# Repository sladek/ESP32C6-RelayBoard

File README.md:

# ESP32C6-RelayBoard
Board with relays and sensors with ESP32C6 SOC.

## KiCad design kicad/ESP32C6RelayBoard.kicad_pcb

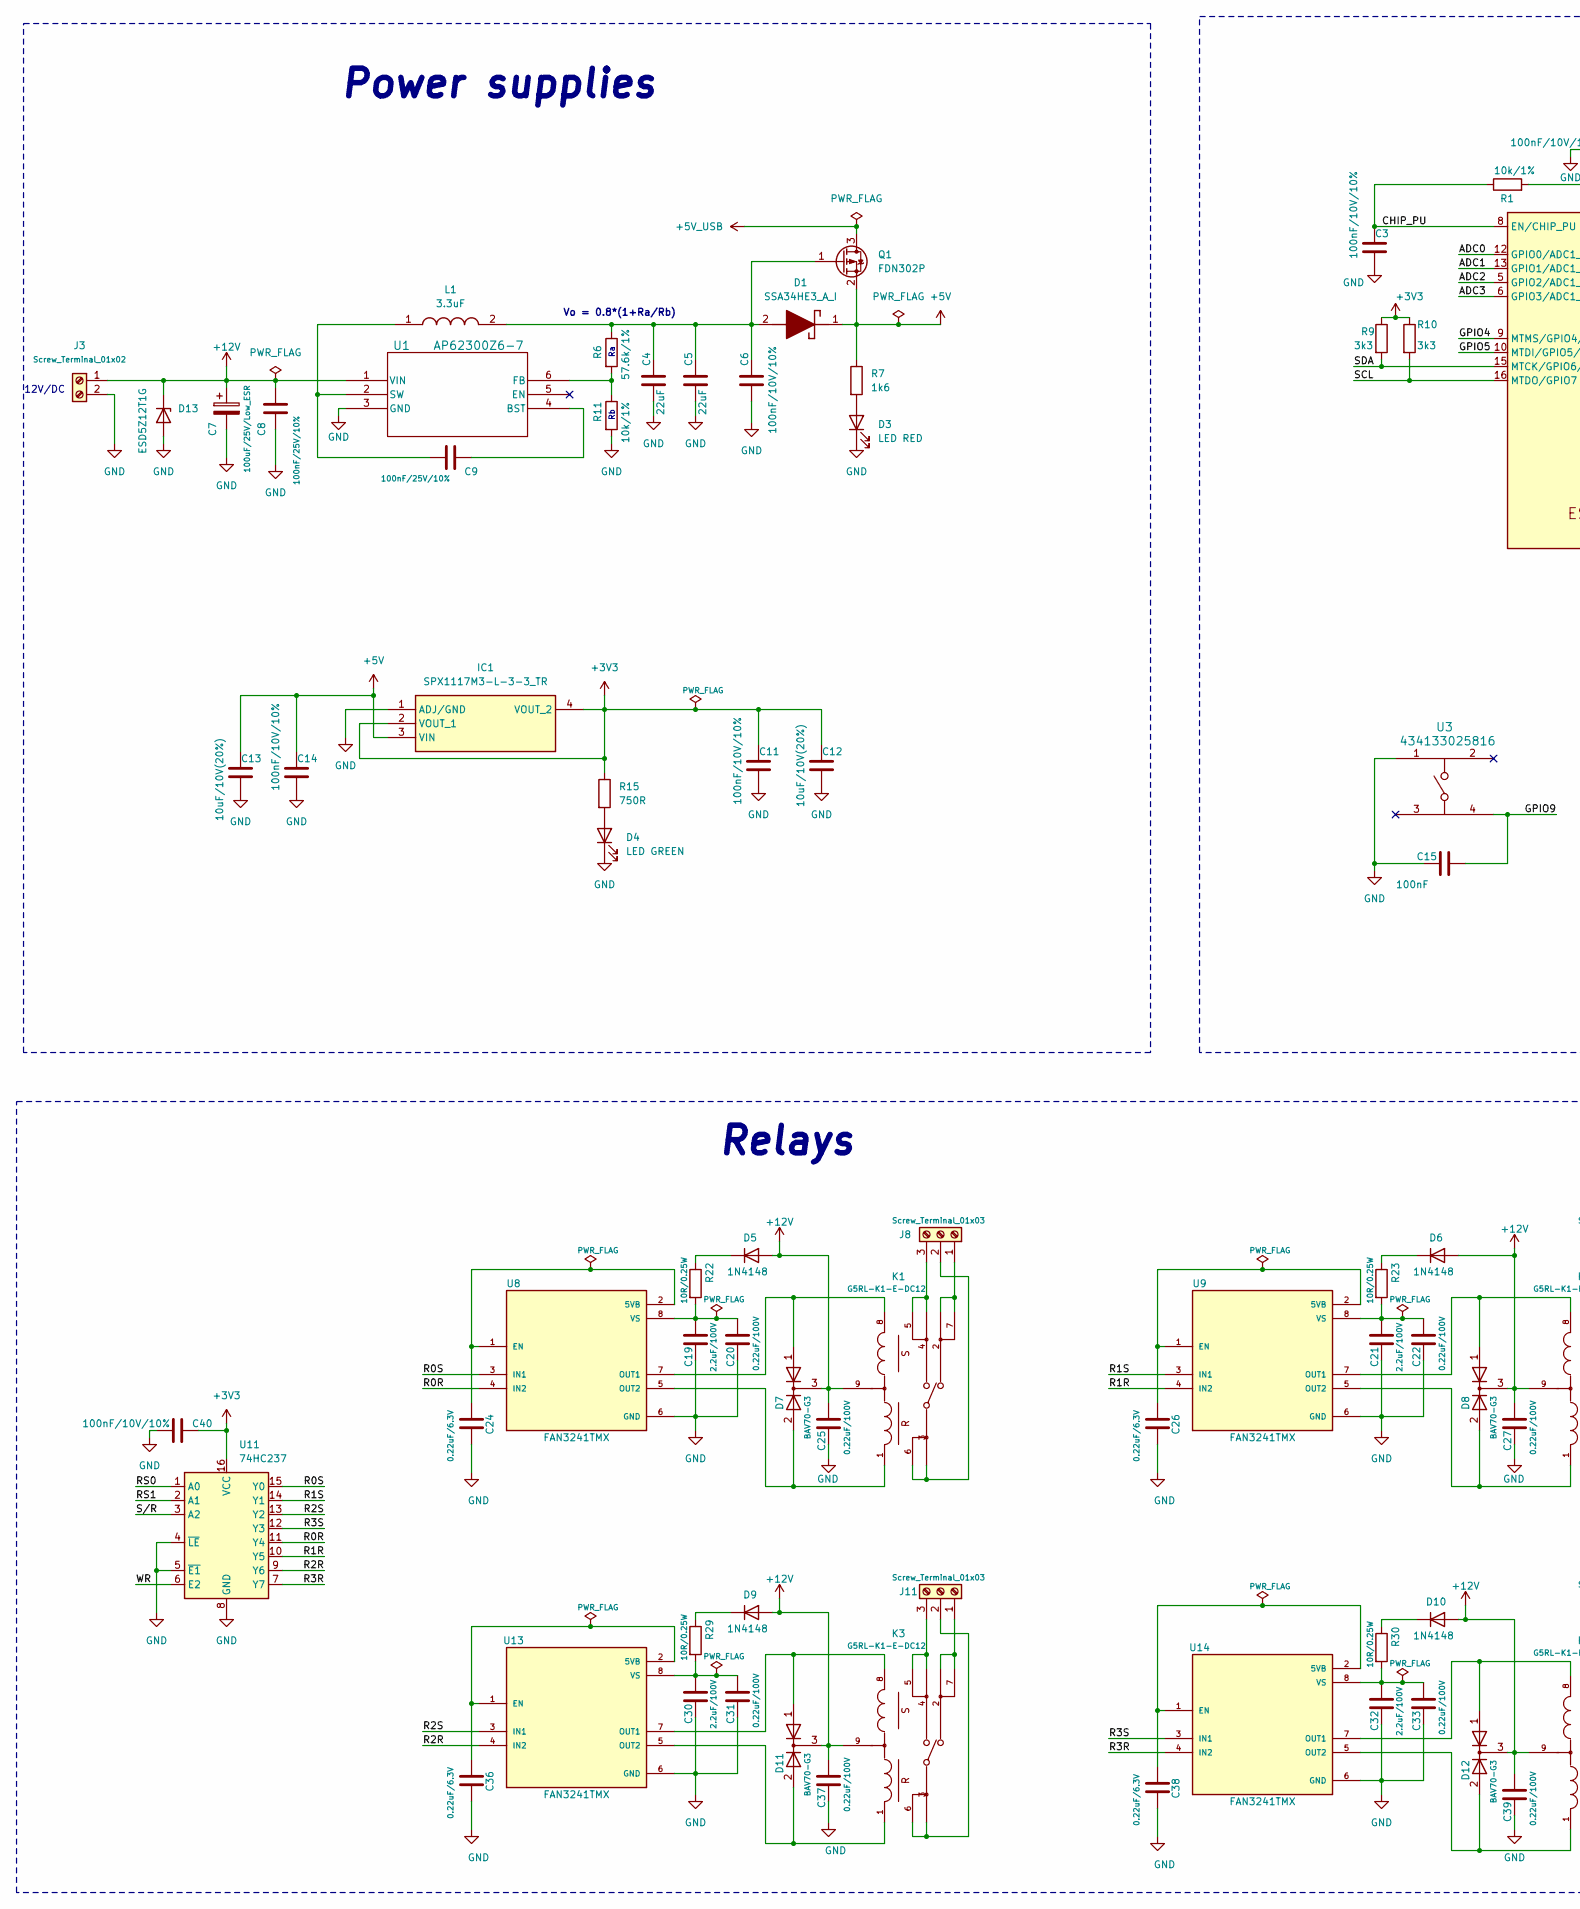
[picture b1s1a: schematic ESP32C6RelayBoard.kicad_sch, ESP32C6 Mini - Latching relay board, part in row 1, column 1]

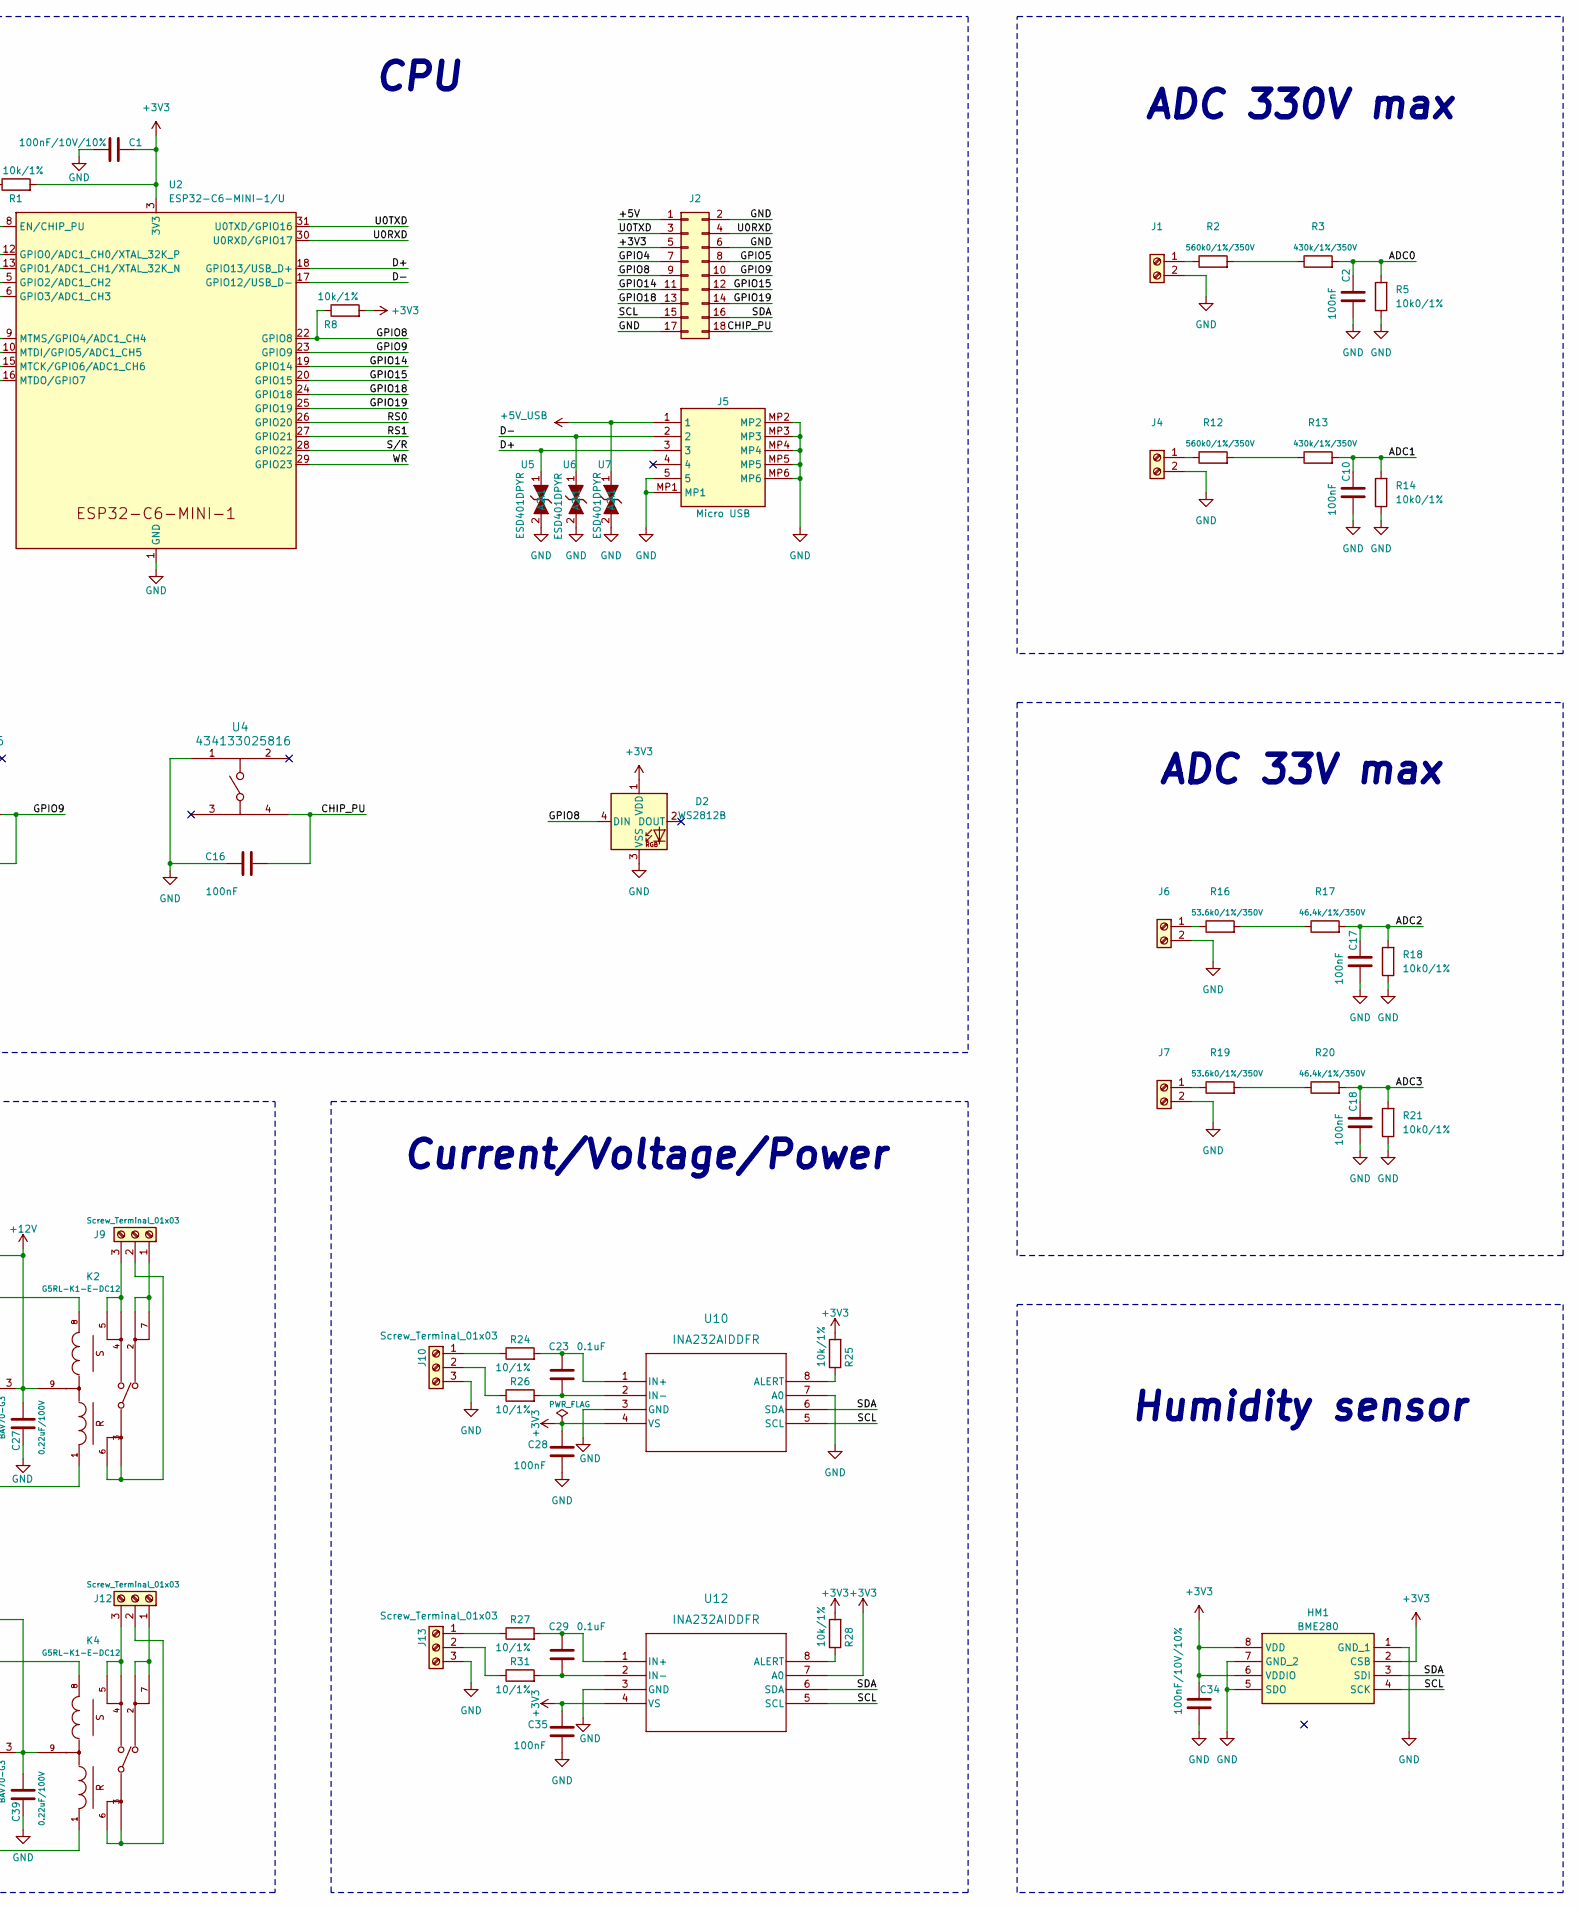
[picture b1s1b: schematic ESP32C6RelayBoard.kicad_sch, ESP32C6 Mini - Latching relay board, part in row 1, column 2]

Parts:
C1, C3, C6, C11, C14, C34, C40: 100nF/10V/10%; C_0201_0603Metric
C2, C10, C15, C16, C17, C18, C28, C35: 100nF; C_0201_0603Metric
C4, C5: 22uF; C_0603_1608Metric
C7: 100uF/25V/Low_ESR; CP_Radial_D6.3mm_P2.50mm
C8, C9: 100nF/25V/10%; C_0603_1608Metric
C12, C13: 10uF/10V(20%); C_0603_1608Metric
C19, C21, C30, C32: 2.2uF/100V; C_1210_3225Metric; Voltage 100V
C20, C22, C25, C27, C31, C33, C37, C39: 0.22uF/100V; C_1206_3216Metric; Voltage 100V
C23, C29: 0.1uF; C_1206_3216Metric
C24, C26, C36, C38: 0.22uF/6.3V; C_1206_3216Metric
D1: SSA34HE3_A_I; DIONM5127X229N; Mouser Part Number 78-SSA34HE3_A/I
D2: WS2812B; LED_WS2812B_PLCC4_5.0x5.0mm_P3.2mm
D3: LED RED; R_0603_1608Metric
D4: LED GREEN; R_0603_1608Metric
D5, D6, D9, D10: 1N4148; SOD3716X145N
D7, D8, D11, D12: BAV70-G3; SOT95P248X115-3N
D13: ESD5Z12T1G; D_SOD-523
HM1: BME280; Mouser Part Number 262-BME280
IC1: SPX1117M3-L-3-3_TR; SOT230P700X180-4N; Mouser Part Number 701-SPX1117M3-L-33TR
J1, J3, J4, J6, J7: Screw_Terminal_01x02; TerminalBlock_Phoenix_MKDS-1,5-2_1x02_P5.00mm_Horizontal
J2: Conn_02x09_Odd_Even; PinHeader_2x09_P2.54mm_Vertical
J5: 10118192-0001LF; 101181920001LF; Mouser Part Number 649-10118192-0001LF
J8, J9, J10, J11, J12, J13: Screw_Terminal_01x03; TerminalBlock_Phoenix_MKDS-1,5-3_1x03_P5.00mm_Horizontal
K1, K2, K3, K4: G5RL-K1-E-DC12; Omron-G5RL-K1-E-MFG; coil voltage 5V; current rating 16A; mouser part number 653-G5RLK1EDC12; digikey description RELAY GEN PURPOSE SPDT 16A 5V
L1: 3.3uF; SRP0315; Mouser Part Number 652-SRP0315
Q1: FDN302P; SOT-23
R1, R8, R11, R25, R28: 10k/1%; R_0603_1608Metric
R2, R12: 560k0/1%/350V; R_0603_1608Metric
R3, R13: 430k/1%/350V; R_0603_1608Metric
R5, R14, R18, R21: 10k0/1%; R_0603_1608Metric
R6: 57.6k/1%; R_0603_1608Metric
R7: 1k6; R_0603_1608Metric
R9, R10: 3k3; R_0603_1608Metric
R15: 750R; R_0603_1608Metric
R16, R19: 53.6k0/1%/350V; R_0603_1608Metric
R17, R20: 46.4k/1%/350V; R_0603_1608Metric
R22, R23, R29, R30: 10R/0.25W; R_1206_3216Metric
R24, R26, R27, R31: 10/1%; R_1206_3216Metric
U1: AP62300Z6-7; SOT563-Z6_1_DIO
U2: ESP32-C6-MINI-1/U; ESP32-C6-MINI-1
U3, U4: 434133025816; SMD_025816_WRE
U5, U6, U7: ESD401DPYR; Mouser Part Number 595-ESD401DPYR
U8, U9, U13, U14: FAN3241TMX; SOIC127P600X175-8N; PARTREV 1.0.2
U10, U12: INA232AIDDFR; SOT65P280X110-8N
U11: 74HC237; SOIC16

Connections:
+3V3: C1.1, C11.1, C12.1, C28.1, C34.1, C35.1, C40.1, D2.1 (VDD), HM1.2 (CSB), HM1.6 (VDDIO), HM1.8 (VDD), IC1.2 (VOUT_1), IC1.4 (VOUT_2), J2.5, R1.2, R8.2, R9.1, R10.1, R15.1, R25.2, R28.2, U2.3 (3V3), U10.4 (VS), U11.16 (VCC), U12.4 (VS), U12.7 (A0)
+5V: C13.1, C14.1, D1.1 (K), IC1.3 (VIN), J2.1, Q1.2 (S), R7.1
+5V_USB: J5.1, Q1.3 (D), U7.1 (A1)
+12V: C7.1, C8.1, C25.1, C27.1, C37.1, C39.1, D5.2 (A), D6.2 (A), D7.3 (K), D8.3 (K), D9.2 (A), D10.2 (A), D11.3 (K), D12.3 (K), D13.1 (K), J3.1, K1.9 (S+/R+), K2.9 (S+/R+), K3.9 (S+/R+), K4.9 (S+/R+), U1.1 (VIN)
/ADC0: C2.2, R3.2, R5.2, U2.12 (GPIO0/ADC1_CH0/XTAL_32K_P)
/ADC1: C10.2, R13.2, R14.2, U2.13 (GPIO1/ADC1_CH1/XTAL_32K_N)
/ADC2: C17.2, R17.2, R18.2, U2.5 (GPIO2/ADC1_CH2)
/ADC3: C18.2, R20.2, R21.2, U2.6 (GPIO3/ADC1_CH3)
/CHIP_PU: C3.1, C16.2, J2.18, R1.1, U2.8 (EN/CHIP_PU), U4.4
/D+: J5.3, U2.18 (GPIO13/USB_D+), U5.1 (A1)
/D-: J5.2, U2.17 (GPIO12/USB_D-), U6.1 (A1)
/GPIO4: J2.7, U2.9 (MTMS/GPIO4/ADC1_CH4)
/GPIO5: J2.8, U2.10 (MTDI/GPIO5/ADC1_CH5)
/GPIO8: D2.4 (DIN), J2.9, R8.1, U2.22 (GPIO8)
/GPIO9: C15.2, J2.10, U2.23 (GPIO9), U3.4
/GPIO14: J2.11, U2.19 (GPIO14)
/GPIO15: J2.12, U2.20 (GPIO15)
/GPIO18: J2.13, U2.24 (GPIO18)
/GPIO19: J2.14, U2.25 (GPIO19)
/R0R: U8.4 (IN2), U11.11 (Y4)
/R0S: U8.3 (IN1), U11.15 (Y0)
/R1R: U9.4 (IN2), U11.10 (Y5)
/R1S: U9.3 (IN1), U11.14 (Y1)
/R2R: U11.9 (Y6), U13.4 (IN2)
/R2S: U11.13 (Y2), U13.3 (IN1)
/R3R: U11.7 (Y7), U14.4 (IN2)
/R3S: U11.12 (Y3), U14.3 (IN1)
/RS0: U2.26 (GPIO20), U11.1 (A0)
/RS1: U2.27 (GPIO21), U11.2 (A1)
/SCL: HM1.4 (SCK), J2.15, R10.2, U2.16 (MTDO/GPIO7), U10.5 (SCL), U12.5 (SCL)
/SDA: HM1.3 (SDI), J2.16, R9.2, U2.15 (MTCK/GPIO6/ADC1_CH6), U10.6 (SDA), U12.6 (SDA)
/S/R: U2.28 (GPIO22), U11.3 (A2)
/U0RXD: J2.4, U2.30 (U0RXD/GPIO17)
/U0TXD: J2.3, U2.31 (U0TXD/GPIO16)
/WR: U2.29 (GPIO23), U11.6 (E2)
GND: C1.2, C2.1, C3.2, C4.2, C5.2, C6.2, C7.2, C8.2, C10.1, C11.2, C12.2, C13.2, C14.2, C15.1, C16.1, C17.1, C18.1, C19.2, C20.2, C21.2, C22.2, C24.1, C25.2, C26.1, C27.2, C28.2, C30.2, C31.2, C32.2, C33.2, C34.2, C35.2, C36.1, C37.2, C38.1, C39.2, C40.2, D2.3 (VSS), D3.1 (K), D4.1 (K), D13.2 (A), HM1.1 (GND_1), HM1.5 (SDO), HM1.7 (GND_2), IC1.1 (ADJ/GND), J1.2, J2.2, J2.6, J2.17, J3.2, J4.2, J5.5, J5.MP1, J5.MP2, J5.MP3, J5.MP4, J5.MP5, J5.MP6, J6.2, J7.2, J10.3, J13.3, R5.1, R11.2, R14.1, R18.1, R21.1, U1.3 (GND), U2.1 (GND), U2.2 (GND), U2.11 (GND), U2.14 (GND), U2.36 (GND), U2.37 (GND), U2.38 (GND), U2.39 (GND), U2.40 (GND), U2.41 (GND), U2.42 (GND), U2.43 (GND), U2.44 (GND), U2.45 (GND), U2.46 (GND), U2.47 (GND), U2.48 (GND), U2.49 (GND), U2.50 (GND), U2.51 (GND), U2.52 (GND), U2.53 (GND), U3.1, U4.1, U5.2 (A2), U6.2 (A2), U7.2 (A2), U8.6 (GND), U9.6 (GND), U10.3 (GND), U10.7 (A0), U11.4 (~LE), U11.5 (~E1), U11.8 (GND), U12.3 (GND), U13.6 (GND), U14.6 (GND)
unnamed: C4.1, C5.1, C6.1, D1.2 (A), L1.2, Q1.1 (G), R6.1
unnamed: D3.2 (A), R7.2
unnamed: D4.2 (A), R15.2
unnamed: D5.1 (K), R22.1
unnamed: D6.1 (K), R23.1
unnamed: D9.1 (K), R29.1
unnamed: D10.1 (K), R30.1
unnamed: J1.1, R2.1
unnamed: J4.1, R12.1
unnamed: J6.1, R16.1
unnamed: J7.1, R19.1
unnamed: J8.1, K1.2, K1.7
unnamed: J8.2, K1.3, K1.6
unnamed: J8.3, K1.4, K1.5
unnamed: J9.1, K2.2, K2.7
unnamed: J9.2, K2.3, K2.6
unnamed: J9.3, K2.4, K2.5
unnamed: J10.1, R24.1
unnamed: J10.2, R26.1
unnamed: J11.1, K3.2, K3.7
unnamed: J11.2, K3.3, K3.6
unnamed: J11.3, K3.4, K3.5
unnamed: J12.1, K4.2, K4.7
unnamed: J12.2, K4.3, K4.6
unnamed: J12.3, K4.4, K4.5
unnamed: J13.1, R27.1
unnamed: J13.2, R31.1
unnamed: D7.2 (A), K1.1 (R-), U8.5 (OUT2)
unnamed: D7.1 (A), K1.8 (S-), U8.7 (OUT1)
unnamed: D8.2 (A), K2.1 (R-), U9.5 (OUT2)
unnamed: D8.1 (A), K2.8 (S-), U9.7 (OUT1)
unnamed: D11.2 (A), K3.1 (R-), U13.5 (OUT2)
unnamed: D11.1 (A), K3.8 (S-), U13.7 (OUT1)
unnamed: D12.2 (A), K4.1 (R-), U14.5 (OUT2)
unnamed: D12.1 (A), K4.8 (S-), U14.7 (OUT1)
unnamed: R2.2, R3.1
unnamed: R12.2, R13.1
unnamed: R16.2, R17.1
unnamed: R19.2, R20.1
unnamed: C9.2, U1.4 (BST)
unnamed: R6.2, R11.1, U1.6 (FB)
unnamed: C9.1, L1.1, U1.2 (SW)
unnamed: C24.2, U8.1 (EN), U8.2 (5VB)
unnamed: C19.1, C20.1, R22.2, U8.8 (VS)
unnamed: C26.2, U9.1 (EN), U9.2 (5VB)
unnamed: C21.1, C22.1, R23.2, U9.8 (VS)
unnamed: R25.1, U10.8 (ALERT)
unnamed: C23.1, R24.2, U10.1 (IN+)
unnamed: C23.2, R26.2, U10.2 (IN-)
unnamed: R28.1, U12.8 (ALERT)
unnamed: C29.1, R27.2, U12.1 (IN+)
unnamed: C29.2, R31.2, U12.2 (IN-)
unnamed: C36.2, U13.1 (EN), U13.2 (5VB)
unnamed: C30.1, C31.1, R29.2, U13.8 (VS)
unnamed: C38.2, U14.1 (EN), U14.2 (5VB)
unnamed: C32.1, C33.1, R30.2, U14.8 (VS)

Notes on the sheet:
Relays
Vo = 0.8*(1+Ra/Rb)
ADC 33V max
Humidity sensor
12V/DC
Current/Voltage/Power
Power supplies
ADC 330V max
CPU

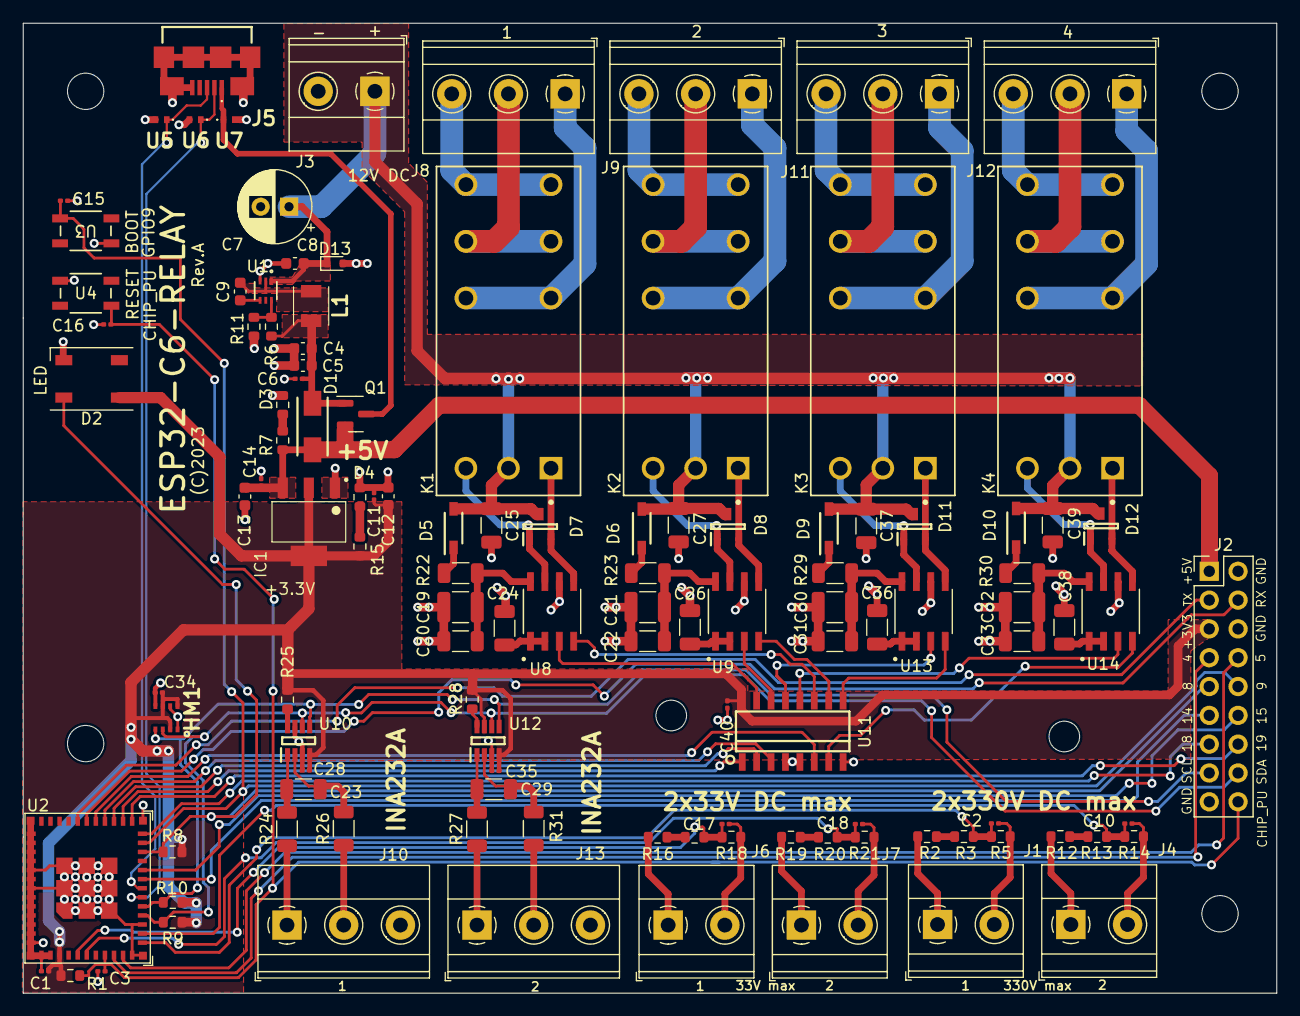
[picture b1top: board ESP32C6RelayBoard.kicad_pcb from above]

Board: 2 copper layers, 110.5 x 85.5 mm, 118 parts (0 on the bottom side), 92 nets.

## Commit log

2023-11-23 Initial version of PCB
2023-11-24 Added LED
2023-11-24 modified .gitignore
2023-11-24 Updated .gitignore and schema
2023-11-24 Added pin names to EXT connector. Generated schema in .pdf.
2023-11-24 Regenerated pictures
2023-11-27 Exposed also SCL and SDO on EXT connector
2023-11-27 Updated PDF for schematics
2023-11-27 Moved buttons and LED away from CPU
2023-12-17 Added 3D models to the project
2023-12-17 fixed pcb footprints with new 3D models
2023-12-17 Added missing 3D models.
2023-12-17 Relays through holes fixed
2023-12-17 Added oversised thermal pads
2023-12-17 Added power planes.
2023-12-17 Updated PCB.

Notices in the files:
kicad/ESP32C6RelayBoard.kicad_pcb:
(C)2023 Rev.A
